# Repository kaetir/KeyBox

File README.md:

# KeyBox

## Équipe

- Antoine VERSMESSEN
- Clément DUQUENNE
- Édouard DANSETTE
- Sébastien WILLEMETZ
- Thibault DESPREZ

## Idées

*gestionnaire de mot de passe physique*

- Utiliser un raspi 0w si possible + usb board
- Écran
    - Oled
- Authentification 
    - Boutons 
    - Lecteur d'empreintes
- Navigation 
    - Boutons

On branche le raspi sur un pc ou un tel pour entrer le mot de passe en auto

Ajout des mots de passe par wifi et/ou physique

Stockage des mots de passe chiffré dans un Json

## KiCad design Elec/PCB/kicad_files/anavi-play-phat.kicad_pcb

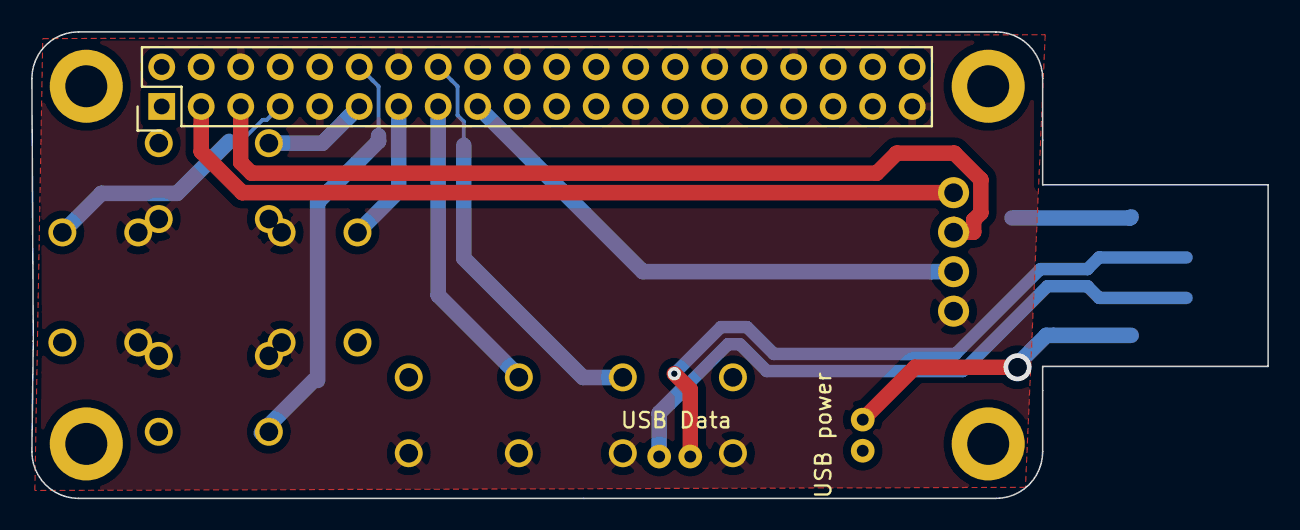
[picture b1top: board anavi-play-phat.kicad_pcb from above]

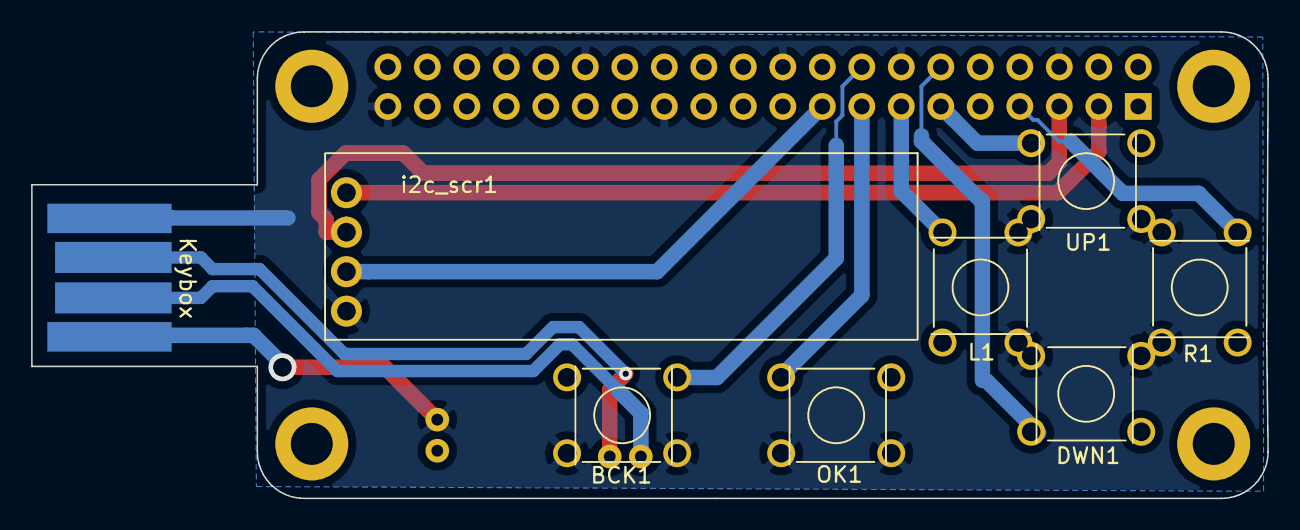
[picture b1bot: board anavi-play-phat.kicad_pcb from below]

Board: 2 copper layers, 79.5 x 30.0 mm, 15 parts (8 on the bottom side), 11 nets.

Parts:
BCK1: boutton_6mx6m; boutton__6mx6m
DWN1: boutton_6mx6m; boutton__6mx6m
J1: USB Data; header 2m spaced
J2: USB power; header 2m spaced
J2#2: USB_A_PLUG; CONN-USB-A-PCB-TRACES
L1: boutton_6mx6m; boutton__6mx6m
OK1: boutton_6mx6m; boutton__6mx6m
R1: boutton_6mx6m; boutton__6mx6m
RASP_CONN1: Raspberry_PI; Pin_Header_Straight_2x20
REF1, REF2, REF3, REF4: MountingHole_2.7mm_M2.5_DIN965_Pad
UP1: boutton_6mx6m; boutton__6mx6m
i2c_scr1: i2c_screen

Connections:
+3V3: RASP_CONN1.1, RASP_CONN1.17, i2c_scr1.VCC
+5V: J2.1, J2#2.1, RASP_CONN1.2, RASP_CONN1.4
GND: BCK1.1, DWN1.1, J2.2, J2#2.4, L1.1, OK1.1, R1.1, RASP_CONN1.6, RASP_CONN1.9, RASP_CONN1.14, RASP_CONN1.20, RASP_CONN1.25, RASP_CONN1.30, RASP_CONN1.34, RASP_CONN1.39, UP1.1, i2c_scr1.GND
unnamed: BCK1.2, RASP_CONN1.16
unnamed: DWN1.2, RASP_CONN1.12
unnamed: L1.2, RASP_CONN1.13
unnamed: OK1.2, RASP_CONN1.15
unnamed: R1.2, RASP_CONN1.7
unnamed: RASP_CONN1.3, i2c_scr1.SDA
unnamed: RASP_CONN1.5, i2c_scr1.SCL
unnamed: RASP_CONN1.11, UP1.2

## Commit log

2019-10-14 ajout du readme et des idées
2019-10-14 ajout des fonctions de base et de test
2019-10-15 code qui permet de cryp et decrypt des mdp a partir d'un mot de passe maitre
2019-10-15 readme update
2019-10-15 ajout d'un code pour écran spi
2019-10-16 patch du nonce
2019-10-16 ouverture et modification de json
2019-10-16 ajout du fichier de test
2019-10-16 passage a des fonctions et test
2019-10-16 ajout de test de code pour les GPIO
2019-10-16 ajout jusqu'a 5 boutons
2019-10-16 wallet fonctionnel
2019-10-17 ajout du server web
2019-10-17 Le cablage des ecrans I2C et SPI et boutons
2019-10-17 restructuration
2019-10-17 update des shemats
2019-10-17 re-update
2019-10-17 serveur avec gestion du formulaire
2019-10-17 intégration du wallet au serveur web
2019-10-17 optimisation d'importation
2019-10-18 Fichiers solidworks
2019-10-18 ajout du code du hotspot
2019-10-18 update du create htm
2019-10-18 ajout du bout de code pour le hotspot
2019-11-07 ajout du descriptif du projet
2019-11-13 fusion des fichiers
2019-11-13 actualisation des cablages I2C et SPI
2019-11-13 PCB test1
2019-11-13 supprimé : hotspot/edit_hostapd_conf.py
2019-11-13 ajout schema
2019-11-13 ajout de l'écran
2019-11-14 wallet link for less duplicate
2019-11-14 Générateur phrase
2019-11-15 ajout de la lecture par un fichier txt
2019-11-15 ajout du fichier txt
2019-11-16 PCB v2
2019-12-02 oled object
2019-12-02 menu as an object
2019-12-02 ajout gitignore
2019-12-02 rm pycache
2019-12-02 Composants
2019-12-02 Il faut refaire le pcb avec le port usb de l'autre coté
2019-12-02 déplacement de la fonction dico dans le genpasswd
    et réencodage du dico en utf8
2019-12-02 commit before leaving
2019-12-03 ajoute des tests de mapping boutons
2019-12-03 Logo Keybox
2019-12-03 PCB v3 correction USB
2019-12-03 Upgrade cursor
2019-12-03 logo mieux
2019-12-03 pcb mieux
2019-12-03 j'avais pas save déso
2019-12-04 Faut ranger
2019-12-04 les changements post zyhto
2019-12-05 entrer alphabet
2019-12-06 export du pcb version 2.5
2019-12-09 alphabet update
2019-12-10 le pcb corrigé pour une vrai prod
2019-12-11 update2 Menu
2019-12-12 Le joli pcb
2019-12-12 les menus quasi terminés
2019-12-13 pcb et readme
2019-12-13 LOL windows cassé
2019-12-13 update menu +wifi
2019-12-13 on ajoute et on nettoie
2019-12-13 menu et gestion du wifi qui marche
2019-12-13 Ajout d'un guide pour configurer le keybox
2019-12-16 un vrai wallet qui remarche
2019-12-16 rename d'une fonction
2019-12-16 poop
2019-12-18 IL EST ECRIT QUE SEUL LONK PEUT VAINCRE GANON
2019-12-18 ouspi copié collé
2019-12-19 Tout plein de modifs
2019-12-20 le web wallet qui marche presque
2019-12-20 petits changements
2019-12-20 first start
2019-12-20 correction ip
2019-12-20 ip toujours
2019-12-20 loop 302
2019-12-20 wallet d'exemple
2019-12-20 python = NULL
2019-12-20 LA GROSSE CALOTE DE TES MORTS TU VAS MANGER
2019-12-20 os.chdir("/home/pi/Keybox")
    os.chdir("/home/pi/Keybox")
2019-12-20 hotspot
